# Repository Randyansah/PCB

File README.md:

- 👋 Hi, I’m @Randyansah
- 👀 I’m interested in ...AI,Embedded systems and IoT 
- 🌱 I’m currently learning ...IoT 
- 💞️ I’m looking to collaborate on ...
- 📫 How to reach me ...randyansah97@gmail.com 

<!---
Randyansah/Randyansah is a ✨ special ✨ repository because its `README.md` (this file) appears on your GitHub profile.
You can click the Preview link to take a look at your changes.
--->

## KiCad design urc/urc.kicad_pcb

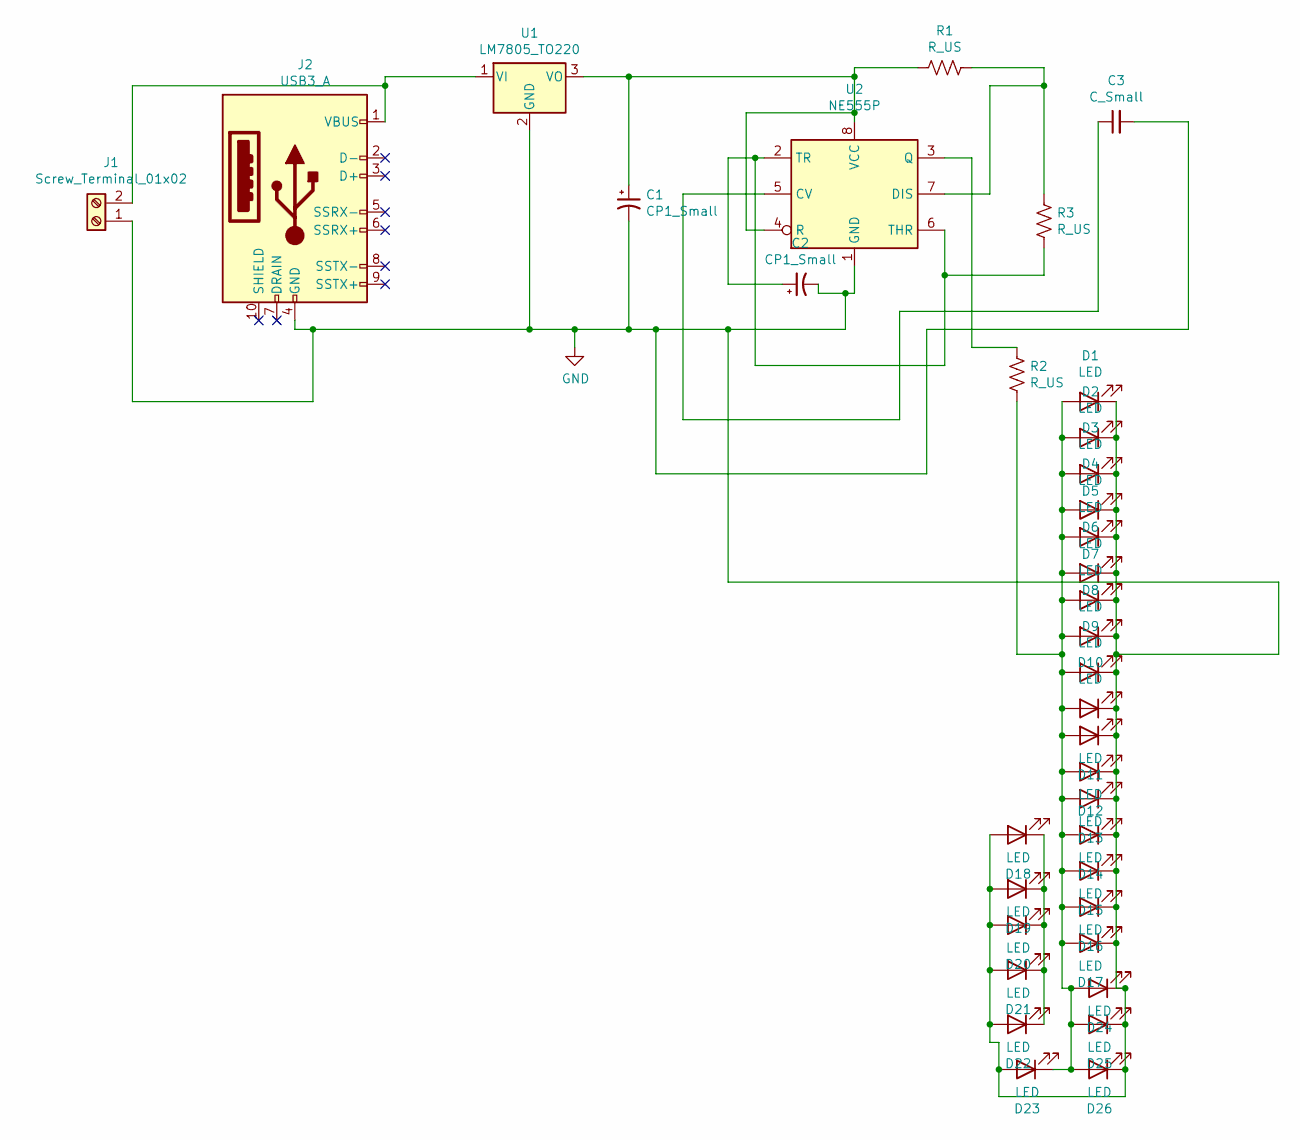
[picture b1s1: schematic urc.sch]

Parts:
C1, C2: CP1_Small; CP_Elec_5x3
C3: C_Small; C_0805_2012Metric
D1, D2, D3, D4, D5, D6, D7, D8, D9, D10, D11, D12, D13, D14, D15, D16, D17, D18, D19, D20, D21, D22, D23, D24, D25, D26: LED; LED_0805_2012Metric
J1: Screw_Terminal_01x02; Altech_AK300_1x02_P5.00mm_45-Degree
J2: USB3_A; USB_A_CNCTech_1001-011-01101_Horizontal
R1, R2, R3: R_US; R_0603_1608Metric
U1: LM7805_TO220; TO-220-3_Vertical
U2: NE555P; DIP-8_W7.62mm

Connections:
GND: C1.2, C2.2, C3.2, D1.1 (K), D2.1 (K), D3.1 (K), D4.1 (K), D5.1 (K), D6.1 (K), D7.1 (K), D8.1 (K), D9.1 (K), D10.1 (K), D11.1 (K), D12.1 (K), D13.1 (K), D14.1 (K), D15.1 (K), D16.1 (K), D17.1 (K), D18.2 (A), D19.2 (A), D20.2 (A), D21.2 (A), D22.2 (A), D23.2 (A), D24.1 (K), D25.1 (K), D26.1 (K), J1.1, J2.4 (GND), U1.2 (GND), U2.1 (GND)
unnamed: C1.1, R1.2, U1.3 (VO), U2.4 (R), U2.8 (VCC)
unnamed: C2.1, R3.2, U2.2 (TR), U2.6 (THR)
unnamed: C3.1, U2.5 (CV)
unnamed: D1.2 (A), D2.2 (A), D3.2 (A), D4.2 (A), D5.2 (A), D6.2 (A), D7.2 (A), D8.2 (A), D9.2 (A), D10.2 (A), D11.2 (A), D12.2 (A), D13.2 (A), D14.2 (A), D15.2 (A), D16.2 (A), D17.2 (A), D23.1 (K), D24.2 (A), D25.2 (A), D26.2 (A), R2.2
unnamed: D18.1 (K), D19.1 (K), D20.1 (K), D21.1 (K), D22.1 (K)
unnamed: J1.2, J2.1 (VBUS), U1.1 (VI)
unnamed: R1.1, R3.1, U2.7 (DIS)
unnamed: R2.1, U2.3 (Q)

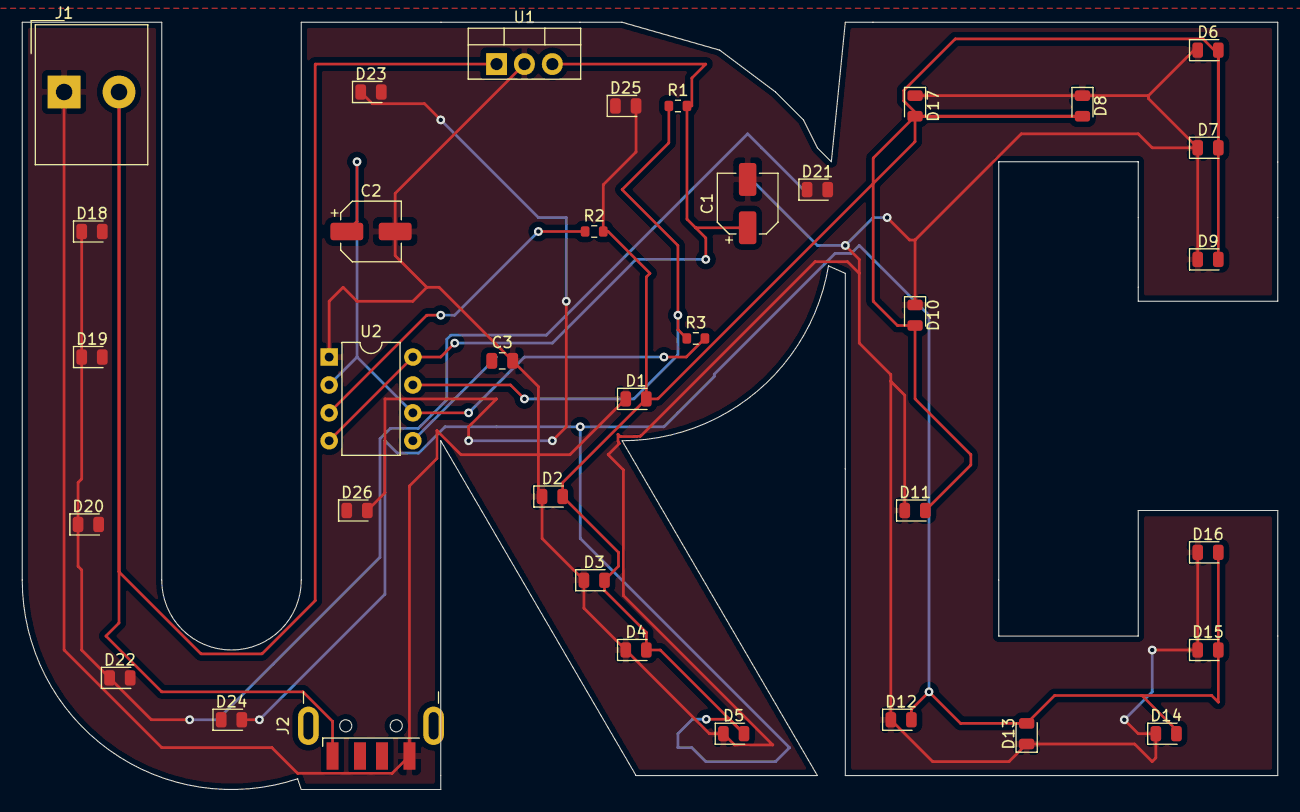
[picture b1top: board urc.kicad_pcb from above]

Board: 2 copper layers, 114.3 x 69.9 mm, 36 parts (0 on the bottom side), 9 nets.

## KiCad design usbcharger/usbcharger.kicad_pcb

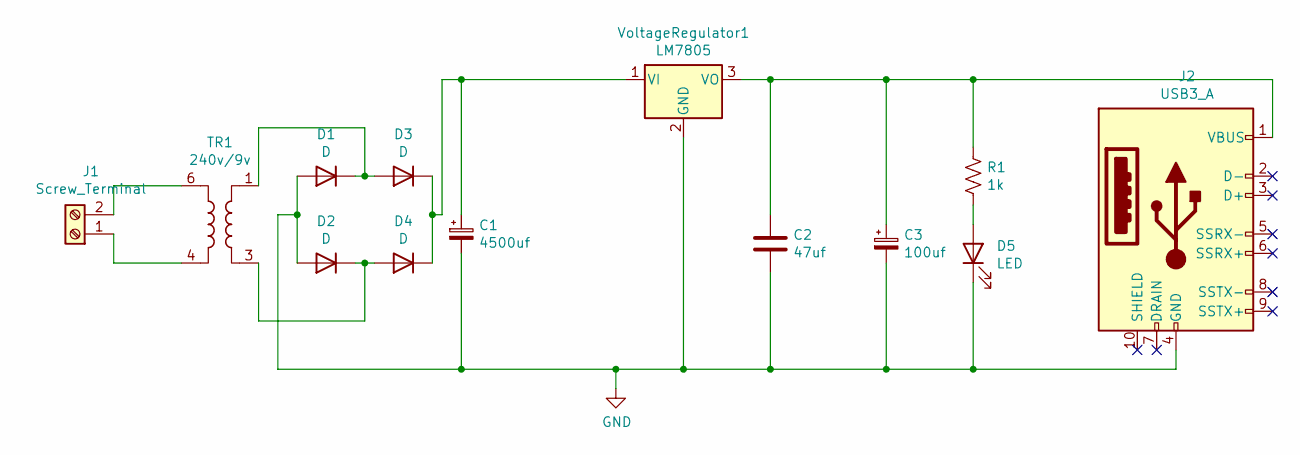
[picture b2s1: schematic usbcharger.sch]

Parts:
C1: 4500uf; CP_Radial_D12.5mm_P2.50mm
C2: 47uf; C_Radial_D4.0mm_H5.0mm_P1.50mm
C3: 100uf; CP_Radial_D6.3mm_P2.50mm
D1, D2, D3, D4: D; D_0402_1005Metric
D5: LED; LED_0201_0603Metric
J1: Screw_Terminal; Altech_AK300_1x02_P5.00mm_45-Degree
J2: USB3_A; USB_A_CNCTech_1001-011-01101_Horizontal
R1: 1k; R_0201_0603Metric
TR1: 240v/9v; Transformer_NF_ETAL_1-1_P1200
VoltageRegulator1: LM7805; TO-220-3_Vertical

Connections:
GND: C1.2, C2.2, C3.2, D1.2 (A), D2.2 (A), D5.1 (K), J2.4 (GND), VoltageRegulator1.2 (GND)
unnamed: C1.1, D3.1 (K), D4.1 (K), VoltageRegulator1.1 (VI)
unnamed: C2.1, C3.1, J2.1 (VBUS), R1.1, VoltageRegulator1.3 (VO)
unnamed: D1.1 (K), D3.2 (A), TR1.1
unnamed: D2.1 (K), D4.2 (A), TR1.3
unnamed: D5.2 (A), R1.2
unnamed: J1.1, TR1.4
unnamed: J1.2, TR1.6

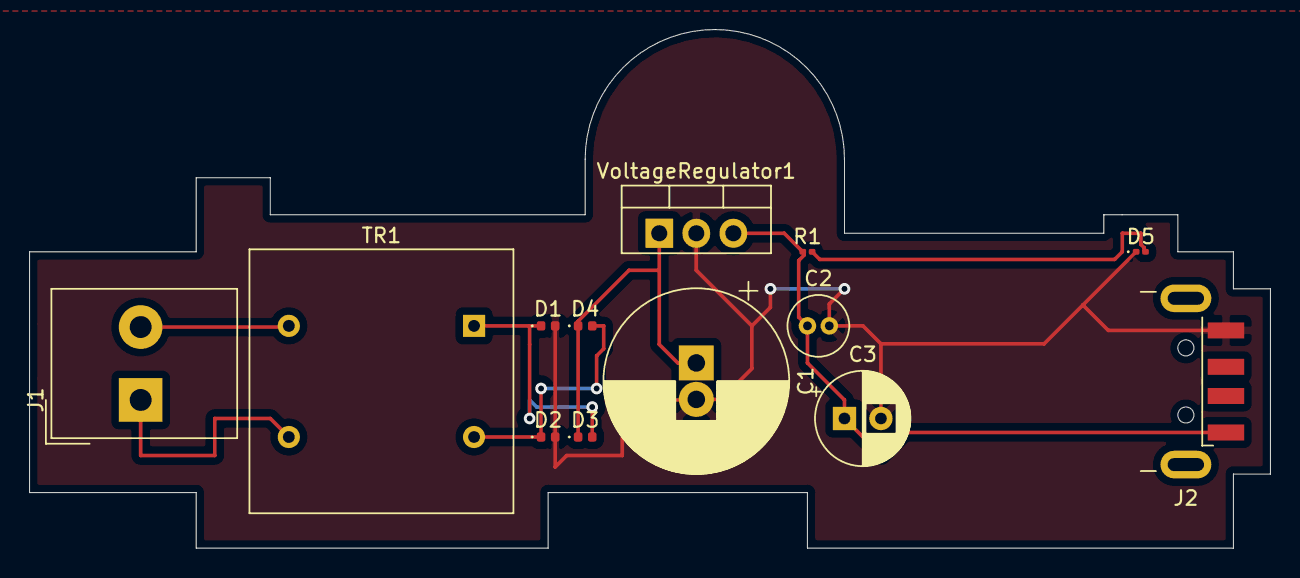
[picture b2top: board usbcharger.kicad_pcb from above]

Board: 2 copper layers, 85.1 x 35.6 mm, 13 parts (0 on the bottom side), 8 nets.

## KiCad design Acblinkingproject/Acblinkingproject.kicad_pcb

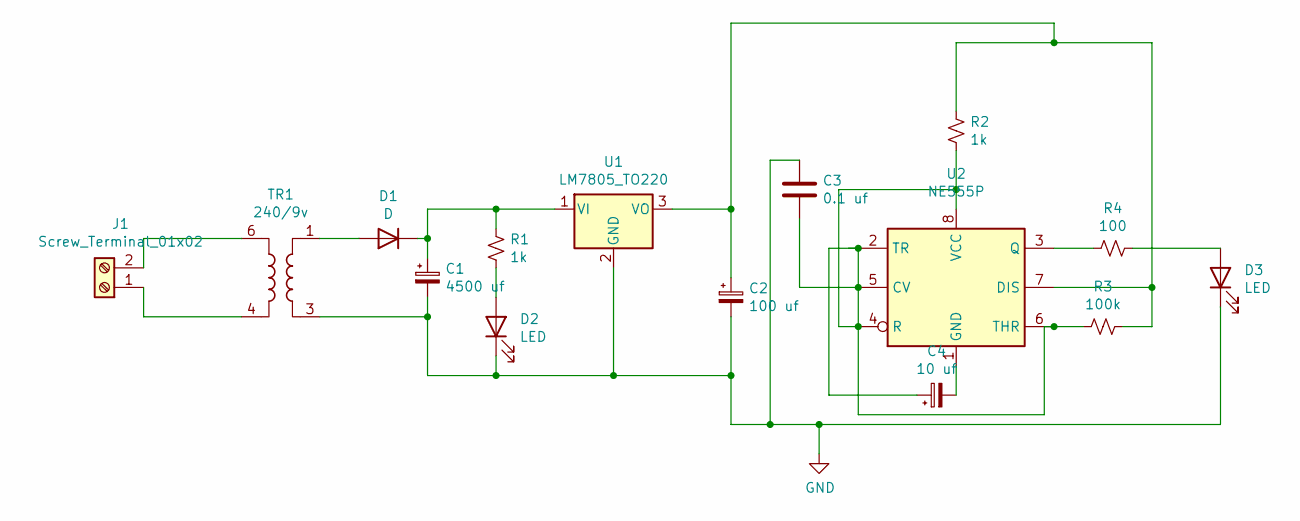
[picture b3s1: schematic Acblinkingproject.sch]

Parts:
C1: 4500 uf; CP_Radial_D25.0mm_P10.00mm_SnapIn
C2: 100 uf; CP_Radial_D4.0mm_P2.00mm
C3: 0.1 uf; C_Radial_D4.0mm_H7.0mm_P1.50mm
C4: 10 uf; CP_Radial_D4.0mm_P1.50mm
D1: D; D_0402_1005Metric
D2, D3: LED; LED_0805_2012Metric
J1: Screw_Terminal_01x02; Altech_AK300_1x02_P5.00mm_45-Degree
R1, R2: 1k; R_0612_1632Metric
R3: 100k; R_0612_1632Metric
R4: 100; R_0612_1632Metric
TR1: 240/9v; Transformer_NF_ETAL_1-1_P1200
U1: LM7805_TO220; TO-220-3_Vertical
U2: NE555P; DIP-8_W7.62mm

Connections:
GND: C1.2, C2.2, C3.1, D2.1 (K), D3.1 (K), TR1.3, U1.2 (GND)
unnamed: C1.1, D1.1 (K), R1.1, U1.1 (VI)
unnamed: C2.1, R2.1, R3.1, U1.3 (VO), U2.7 (DIS)
unnamed: C3.2, C4.1, R2.2, R3.2, U2.2 (TR), U2.4 (R), U2.5 (CV), U2.6 (THR), U2.8 (VCC)
unnamed: C4.2, U2.1 (GND)
unnamed: D1.2 (A), TR1.1
unnamed: D2.2 (A), R1.2
unnamed: D3.2 (A), R4.1
unnamed: J1.1, TR1.4
unnamed: J1.2, TR1.6
unnamed: R4.2, U2.3 (Q)

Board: 2 copper layers, 15 parts (0 on the bottom side), 11 nets, no tracks yet.

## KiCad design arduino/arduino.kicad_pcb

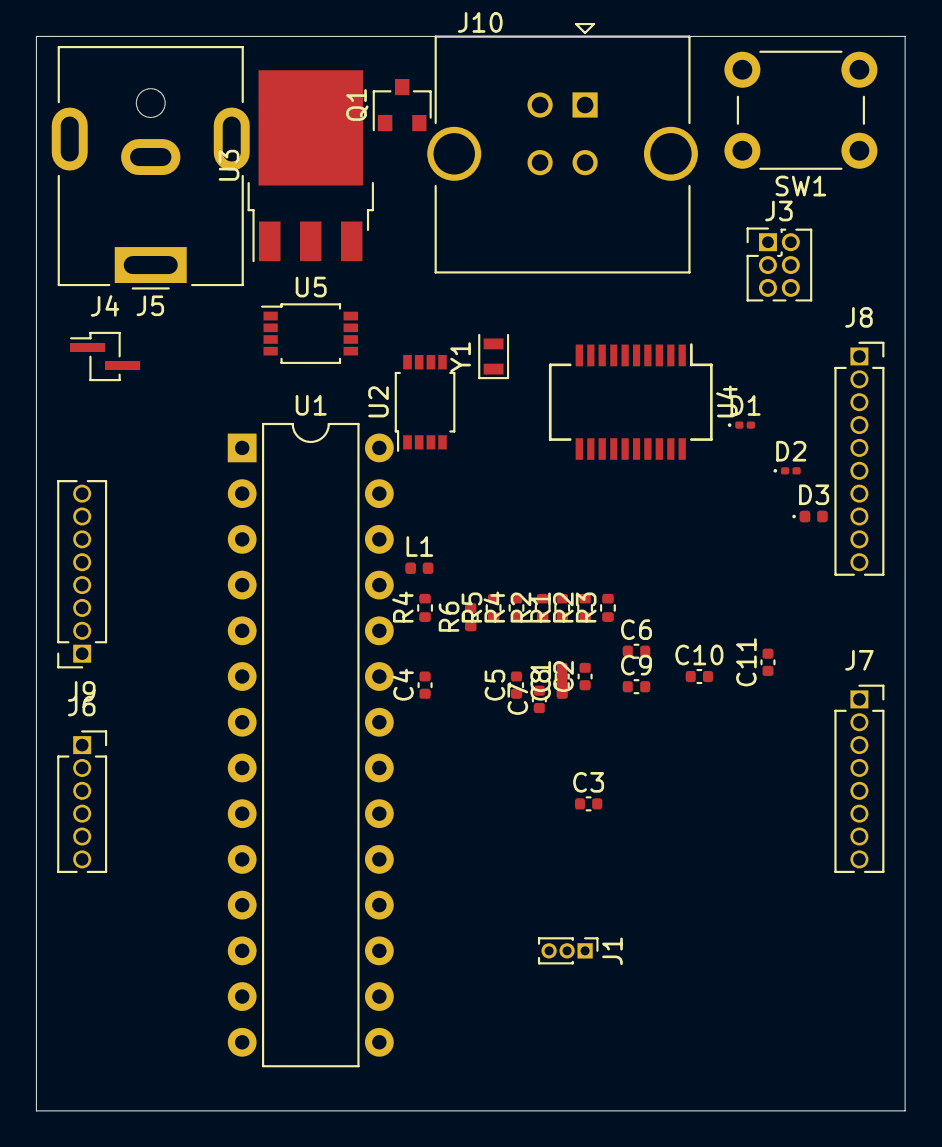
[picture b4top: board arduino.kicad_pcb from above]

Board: 2 copper layers, 48.3 x 59.7 mm, 40 parts (0 on the bottom side), 39 nets, no tracks yet.

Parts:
C1, C2, C9, C10, C11: 100nF; C_0402_1005Metric
C3: C_Small; C_0402_1005Metric
C4, C7, C8: 100uF; C_0402_1005Metric
C5, C6: 22pf; C_0402_1005Metric
D1, D2: LED; LED_0201_0603Metric
D3: D; D_0402_1005Metric
J1: Conn_01x03; PinHeader_1x03_P1.00mm_Vertical
J3: Conn_02x03_Odd_Even; PinHeader_2x03_P1.27mm_Vertical
J4: Conn_01x02; PinSocket_1x02_P1.00mm_Vertical_SMD_Pin1Left
J5: Barrel_Jack_Switch; BarrelJack_CUI_PJ-063AH_Horizontal
J6: Conn_01x06; PinSocket_1x06_P1.27mm_Vertical
J7, J9: Conn_01x08; PinSocket_1x08_P1.27mm_Vertical
J8: Conn_01x10; PinSocket_1x10_P1.27mm_Vertical
J10: USB_B; USB_B_TE_5787834_Vertical
L1: INDUCTOR; L_0402_1005Metric
Q1: FDN340P; SOT-23
R1, R3: 330E; R_0402_1005Metric
R2: 390E; R_0402_1005Metric
R2#2, R4#2, R5, R6: 10k; R_0402_1005Metric
R4: 240E; R_0402_1005Metric
SW1: SW_MEC_5E; SW_PUSH_6mm_H8mm
U1: ATmega328P-PU; DIP-28_W7.62mm
U2, U5: LMV358; OnSemi_Micro8
U3: L7805; TO-252-3_TabPin2
U4: FT232RL; SSOP-20_3.9x8.7mm_P0.635mm
Y1: Crystal_Small; Crystal_SMD_2012-2Pin_2.0x1.2mm

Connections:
3.3V: C4.1, J9.5, R4.1, U2.2
5V: C8.1, C9.1, J1.1, U3.3
5VUSB: J1.3, Q1.3, R6.1
A0: J6.6, U1.23
A1: J6.5, U1.24
A2: J6.4, U1.25
A3: J6.3, U1.26
A4: J6.2, U1.27
A5: J6.1, U1.28
D2: J7.3, U1.4
D3: J7.4, U1.5
D4: J7.5, U1.6
D5: J7.6, U1.11
D6: J7.7, U1.12
D7: J7.8, U1.13
D8: J8.1, U1.14
D9: J8.2, U1.15
D10: J8.3, U1.16
D11: J3.4, J8.4, U1.17
D12: J3.1, J8.5, U1.18
D13: J3.3, J8.6, R3.1, U1.19
GNDREF: C1.1, C2.1, C3.1, C4.2, C5.1, C6.1, C7.2, C8.2, C9.2, C10.1, C11.2, D1.1, D2.1, J3.6, J4.1, J5.2, J8.7, J8.9, J9.2, J9.3, J10.4, L1.2, R2.2, R4#2.2, SW1.1, SW1.2, U1.8, U1.22, U3.2, U4.7, U4.18
unnamed: C5.2, U1.9, Y1.1
unnamed: C6.2, U1.10, Y1.2
unnamed: C10.2, C11.1, J10.2, J10.3, U4.4, U4.15, U4.16, U4.17, U4.19, U4.20
unnamed: D1.2, R1.2
unnamed: D2.2, R3.2
unnamed: D3.1, J4.2, U3.1
unnamed: D3.2, J5.1
unnamed: J10.1, R6.2
unnamed: J10.5, L1.1
unnamed: Q1.1, U5.1, U5.2
unnamed: R2.1, R2#2.1, R4.2, R4#2.1, U2.3
unnamed: U2.1, U5.3
Reset: J3.5, J9.6, R5.2, U1.1, U4.2
Rx: J7.1, U1.2, U4.1
Tx: J7.2, U1.3, U4.5
VCC: C1.2, C3.2, J1.2, J3.2, J8.8, J8.10, J9.4, J9.7, R1.1, R5.1, U1.7, U1.20, U1.21
Vin: C2.2, C7.1, J9.1, R2#2.2

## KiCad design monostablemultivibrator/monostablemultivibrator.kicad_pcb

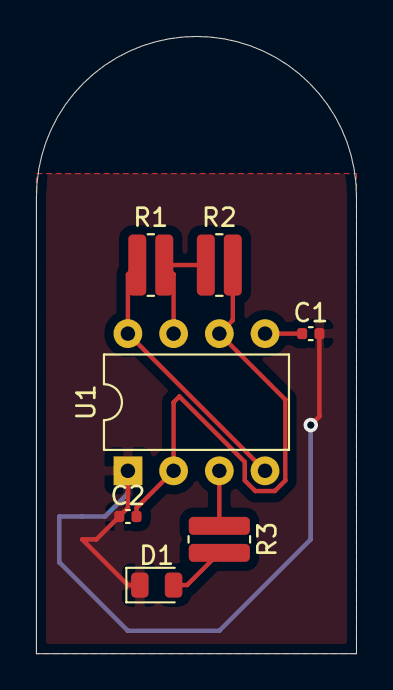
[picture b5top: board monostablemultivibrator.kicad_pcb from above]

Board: 2 copper layers, 17.8 x 34.3 mm, 7 parts (0 on the bottom side), 7 nets.

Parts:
C1: 0.1 uf; C_0402_1005Metric
C2: 103; C_0402_1005Metric
D1: LED; LED_0805_2012Metric
R1: 1K; R_0612_1632Metric
R2: 100K; R_0612_1632Metric
R3: 100; R_0612_1632Metric
U1: NE555P; DIP-8_W7.62mm

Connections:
GND: C1.2, C2.1, D1.1, U1.1
unnamed: C1.1, U1.5
unnamed: C2.2, R2.2, U1.2, U1.6
unnamed: D1.2, R3.2
unnamed: R1.2, R2.1, U1.7
unnamed: R3.1, U1.3
VDD: R1.1, U1.4, U1.8

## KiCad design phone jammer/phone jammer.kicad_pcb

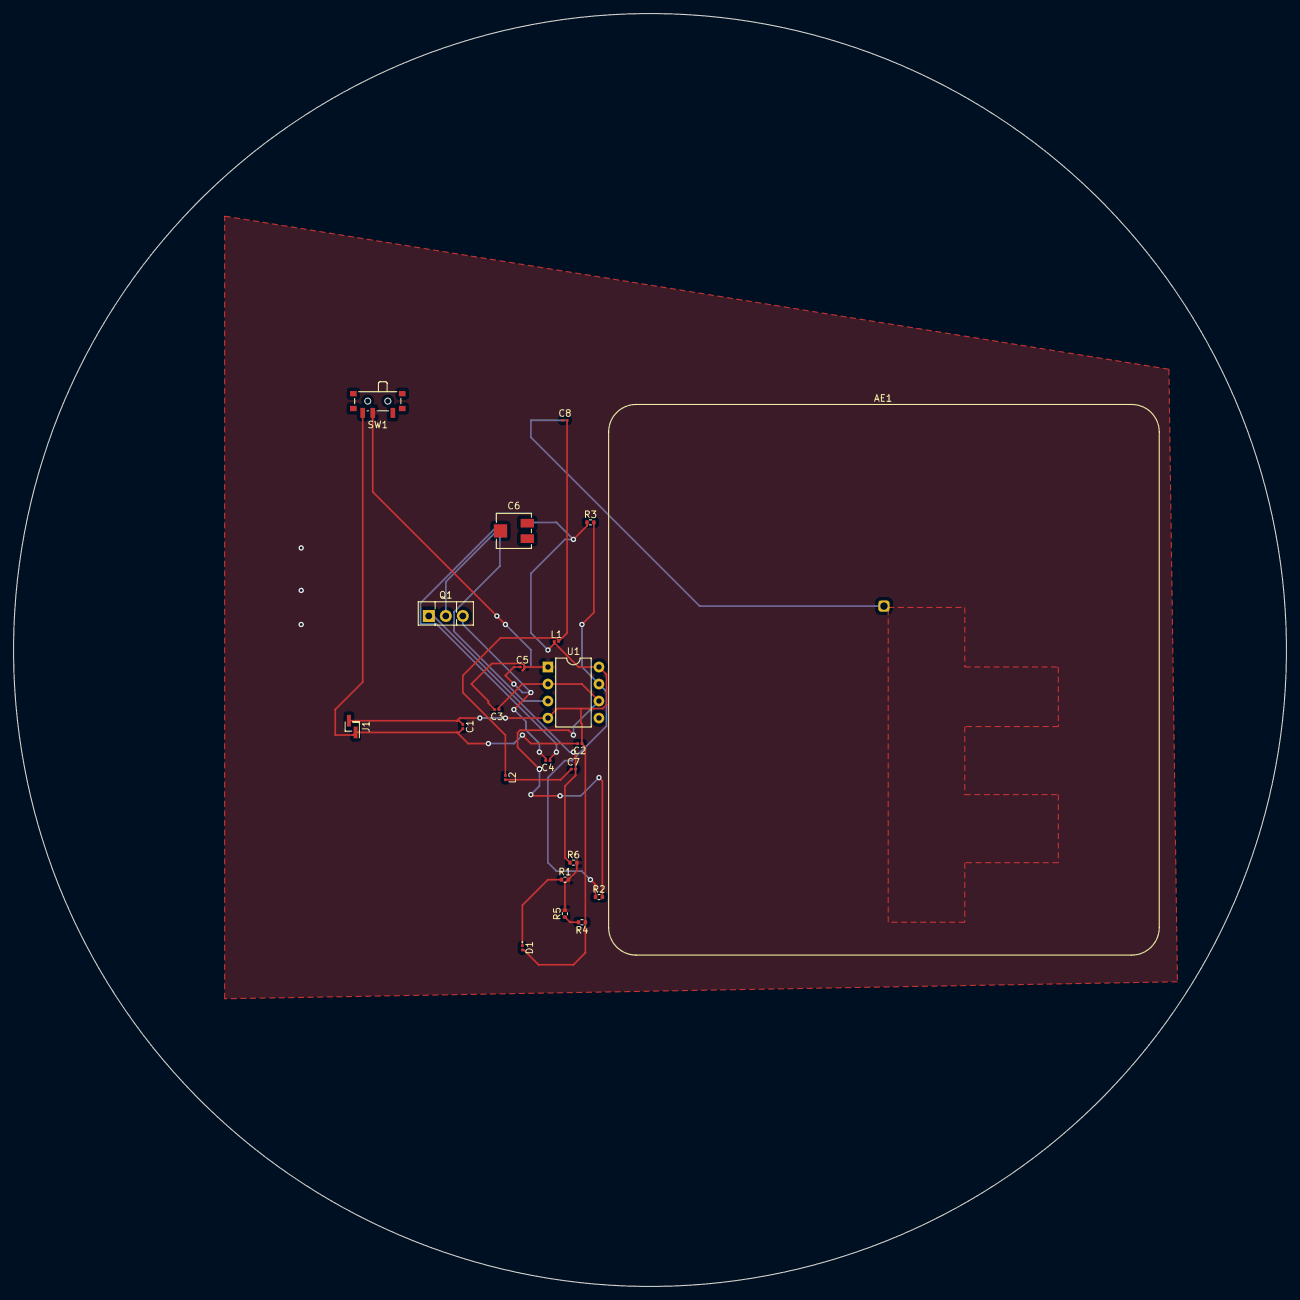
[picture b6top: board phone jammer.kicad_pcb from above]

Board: 2 copper layers, 190.0 x 190.0 mm, 22 parts (0 on the bottom side), 14 nets.

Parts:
AE1: 15 turn 24 AWG; Abracon_APAES868R8060C16-T
C1, C5: 47 uf; C_0201_0603Metric
C2: 0.1 uf; C_0201_0603Metric
C3: 3.3 pf; C_0201_0603Metric
C4: 4.7 uf; C_0201_0603Metric
C6: 30 pf trimmer; Potentiometer_Vishay_TS53YJ_Vertical
C7: 2 pf; C_0201_0603Metric
C8: 4.7 pF; C_0201_0603Metric
D1: LED; LED_0201_0603Metric
J1: Conn_01x02; PinHeader_1x02_P1.00mm_Vertical_SMD_Pin1Right
L1: 4 Turn 24 AWG; L_0201_0603Metric
L2: L; L_0201_0603Metric
Q1: BF459; TO-126-3_Vertical
R1: 220; R_0402_1005Metric
R2: 82 K; R_0402_1005Metric
R3: 6.8K; R_0402_1005Metric
R4: 10K; R_0402_1005Metric
R5: 5.6K; R_0402_1005Metric
R6: 220 E; R_0402_1005Metric
SW1: SW_SPDT; SW_SPDT_PCM12
U1: NE555P; DIP-8_W7.62mm

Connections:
GNDREF: C3.2, C5.2, R1.2, R5.2, R6.2, SW1.2, U1.1
unnamed: AE1.1, C8.1
unnamed: C1.2, C2.2, J1.1, SW1.3
unnamed: C3.1, R2.2, U1.2, U1.6
unnamed: C4.1, U1.3
unnamed: C4.2, C5.1, Q1.3
unnamed: C6.2, Q1.2
unnamed: C7.1, L2.2
unnamed: C7.2, Q1.1, R6.1
unnamed: C8.2, L1.2, L2.1
unnamed: D1.1, R1.1
unnamed: R2.1, R3.2, U1.7
unnamed: R4.2, R5.1
VDD: C1.1, C2.1, C6.1, D1.2, J1.2, L1.1, R3.1, R4.1, U1.4, U1.8
